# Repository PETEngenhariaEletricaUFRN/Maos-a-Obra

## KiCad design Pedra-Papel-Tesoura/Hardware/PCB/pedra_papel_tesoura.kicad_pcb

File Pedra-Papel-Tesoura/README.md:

# Pedra-Papel-Tesoura

## Componentes

- ESP32 DevKit 30 pinos (USB-C)
- Display OLED 0,96" I2C
- Sensor ultrassônico HC-SR04
- Resistores 2,2k e 3,3k (divisor do ECHO)
- Capacitores 2x 100nF e 2x 10uF
- 2 barras de pino fêmea 1x4

## Ligações

| ESP32 | Vai para |
|---|---|
| GPIO21 | SDA do display |
| GPIO22 | SCL do display |
| GPIO5 | TRIG do sensor |
| GPIO18 | ECHO do sensor (pelo divisor) |
| 3V3 | VCC do display |
| VIN | VCC do sensor |
| GND | GND |

## Código

Feito no ESP-IDF (versão 5.3 ou mais nova).

```
cd Software/ESP-IDF
idf.py set-target esp32
idf.py build flash monitor
```

## Placa

Feita para fresadora, com todos os componentes soldados por baixo. A trilha de cima liga as duas vias; se os furos não forem metalizados, passa um fio nelas e solda dos dois lados.

## Case

4 peças em PLA ou PETG: as duas metades do corpo e os dois pés. Encaixa a placa, fecha as metades e desliza os pés até travar.

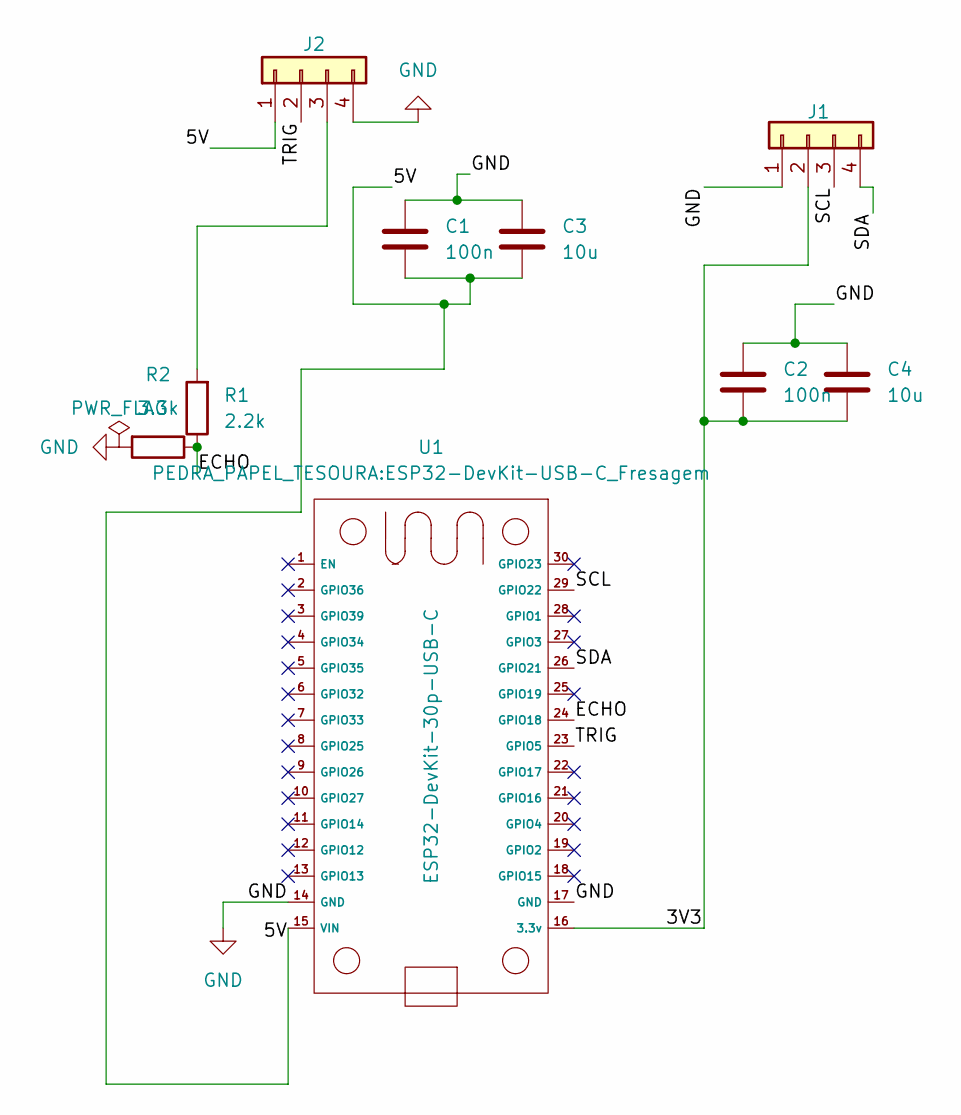
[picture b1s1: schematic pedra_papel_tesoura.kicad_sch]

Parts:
C1, C2: 100n; C_0805_2012Metric
C3, C4: 10u; C_0805_2012Metric
J1: Conn_01x04; PinSocket_1x04_P2.54mm_Vertical_Fresagem
J2: Conn_01x04; PinSocket_1x04_P2.54mm_Horizontal_Fresagem
R1: 2.2k; R_0805_2012Metric
R2: 3.3k; R_0805_2012Metric
U1: ESP32-DevKit-30p-USB-C; ESP32-DevKit-USB-C_Fresagem

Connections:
/3V3: C2.1, C4.1, J1.2, U1.16 (GND)
/5V: C1.1, C3.1, J2.1, U1.15 (GND)
/ECHO: R1.1, R2.1, U1.24 (GND)
/SCL: J1.3, U1.29 (TX)
/SDA: J1.4, U1.26 (IO9)
/TRIG: J2.2, U1.23 (IO7)
GND: C1.2, C2.2, C3.2, C4.2, J1.1, J2.4, R2.2, U1.14 (5V), U1.17 (IO19)
unnamed: J2.3, R1.2

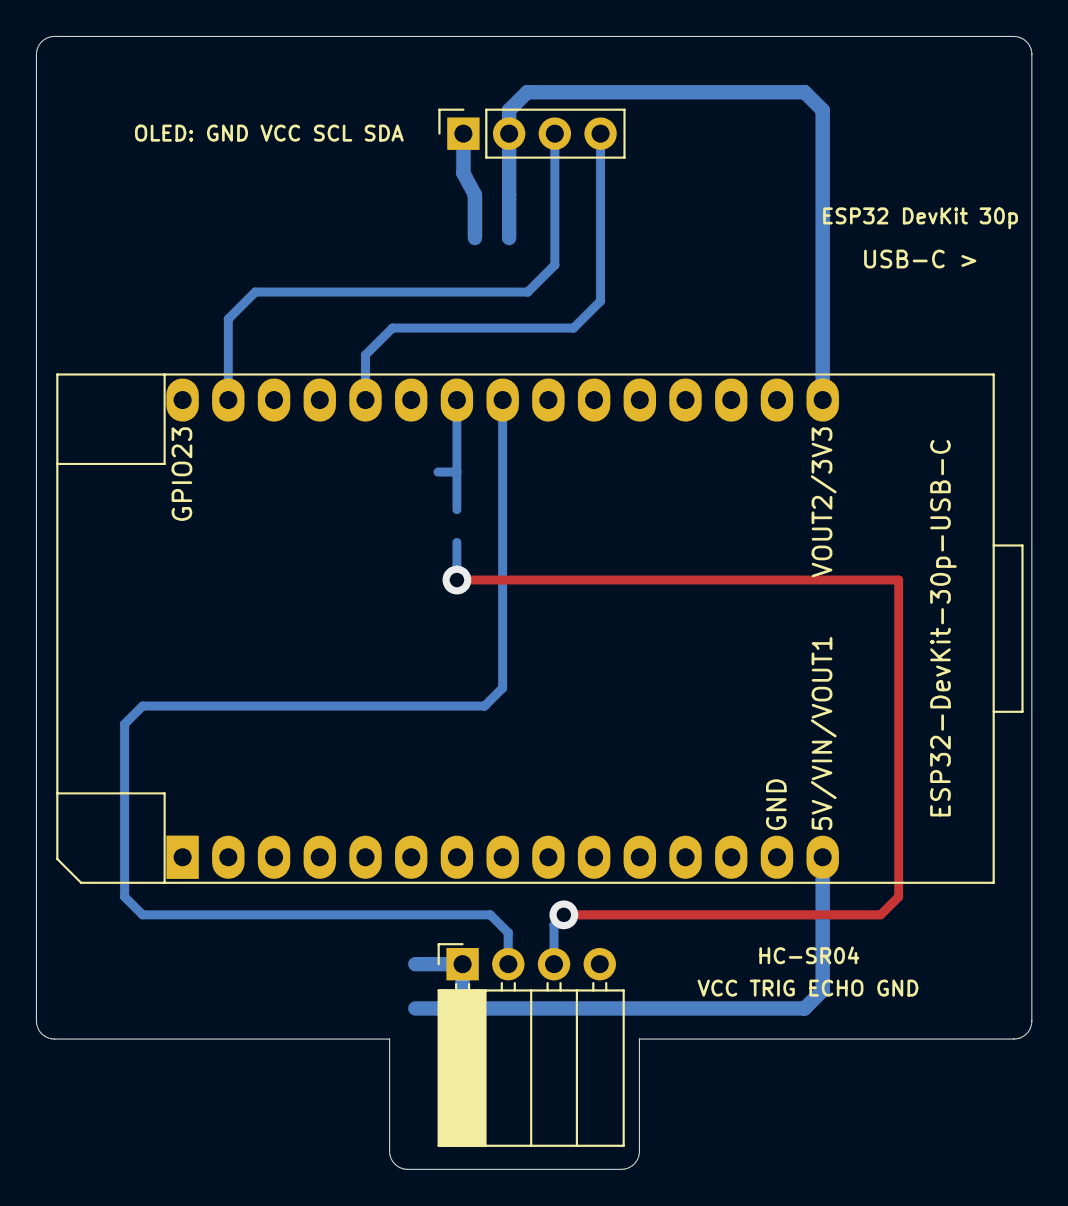
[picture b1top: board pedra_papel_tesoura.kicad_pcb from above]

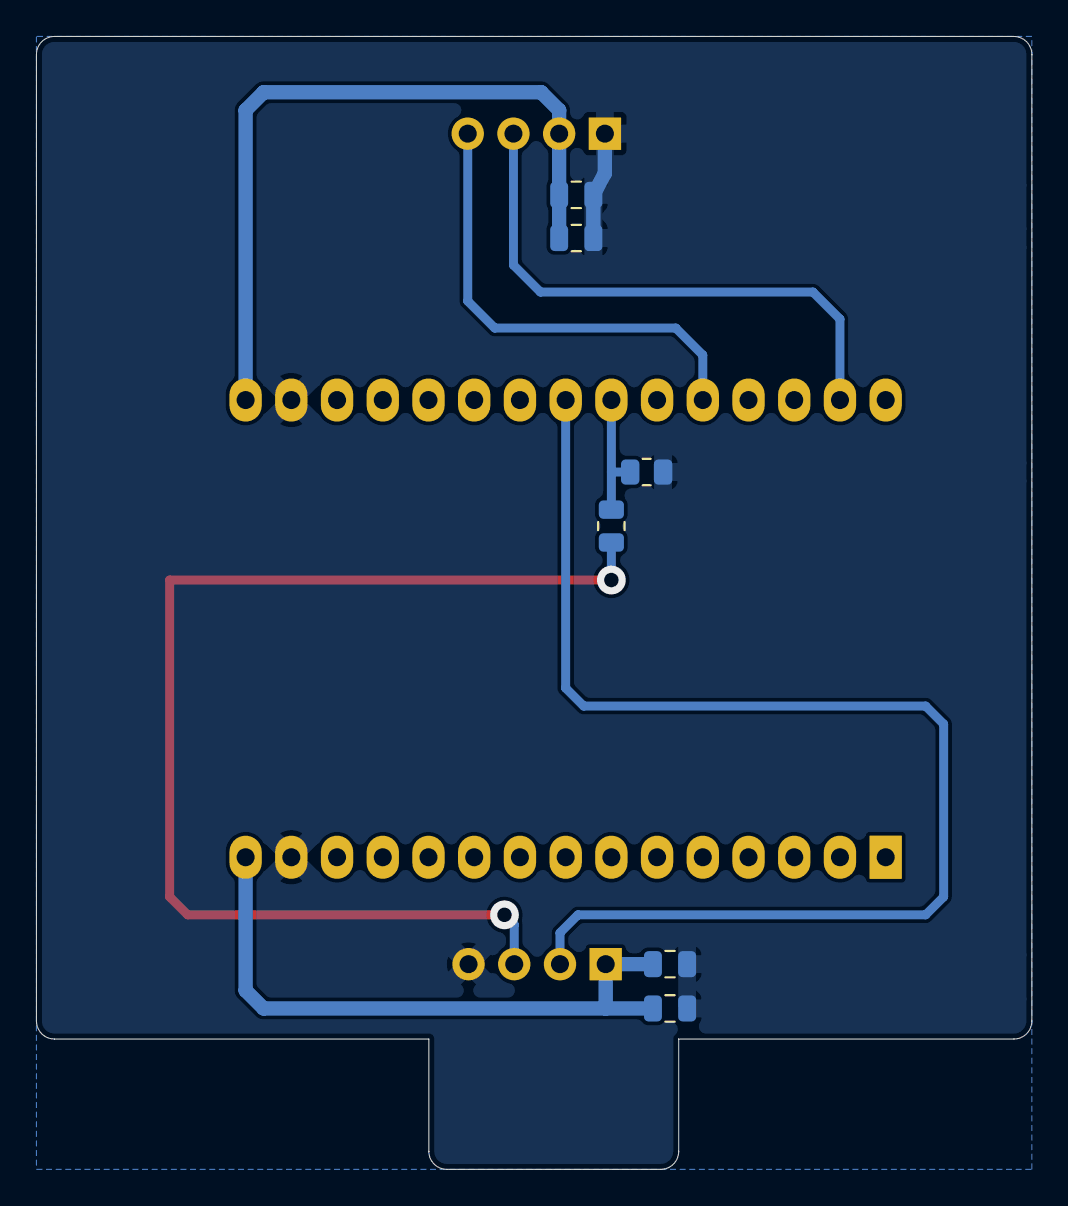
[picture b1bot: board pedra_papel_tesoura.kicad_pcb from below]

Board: 2 copper layers, 55.3 x 62.9 mm, 9 parts (6 on the bottom side), 8 nets.
